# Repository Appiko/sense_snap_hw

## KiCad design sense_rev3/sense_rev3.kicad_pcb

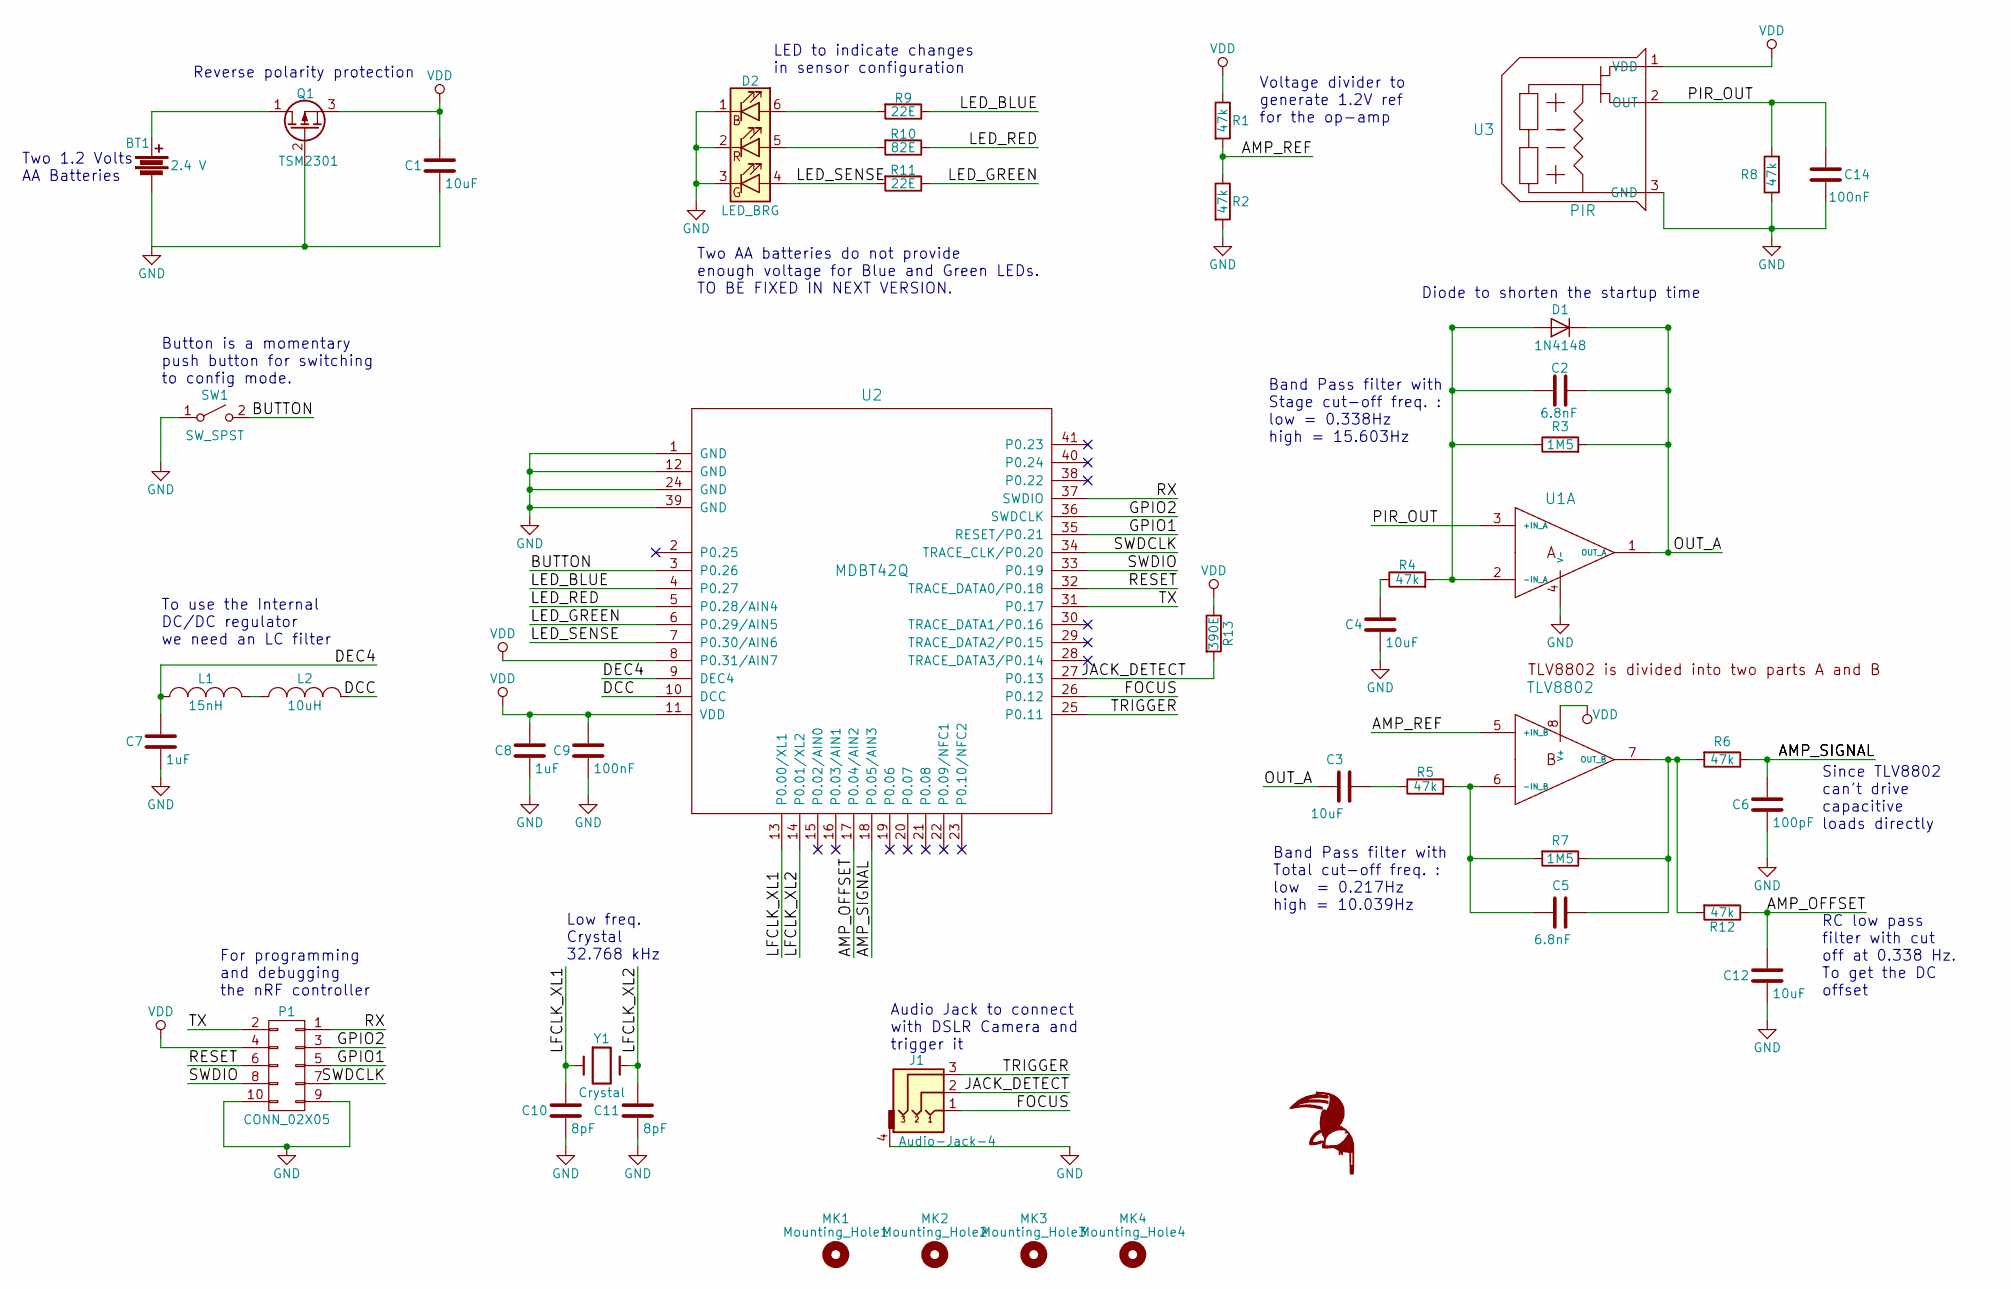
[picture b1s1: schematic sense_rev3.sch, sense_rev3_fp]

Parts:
BT1: 2.4 V; Molex_KK-6410-02_02x2.54mm_Straight
C1, C3, C4, C12: 10uF; C_0805
C2, C5: 6.8nF; C_0805
C6: 100pF; C_0805
C7, C8: 1uF; C_0805
C9, C14: 100nF; C_0805
C10, C11: 8pF; C_0805
D1: 1N4148; D_MiniMELF
D2: LED_BRG; LED_RGB_5050-6
J1: Audio-Jack-4; Molex_KK-6410-04_04x2.54mm_Straight
L1: 15nH; L_0805
L2: 10uH; L_0805
MK1: Mounting_Hole1; MountingHole_3.2mm_M3
MK2: Mounting_Hole2; MountingHole_3.2mm_M3
MK3: Mounting_Hole3; MountingHole_3.2mm_M3
MK4: Mounting_Hole4; MountingHole_3.2mm_M3
P1: CONN_02X05; prog_connect
Q1: TSM2301; SOT-23
R1, R2, R4, R5, R6, R8, R12: 47k; R_0805
R3, R7: 1M5; R_0805
R9, R11: 22E; R_0805
R10: 82E; R_0805
R13: 390E; R_0805
SW1: SW_SPST; Molex_KK-6410-02_02x2.54mm_Straight
U1: TLV8802; SSOP-8_2.95x2.8mm_Pitch0.65mm
U2: MDBT42Q; mdbt42Q
U3: PIR; PIR_TO5
Y1: Crystal; Crystal_C38-LF_d3.0mm_l8.0mm_Horizontal

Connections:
/AMP_OFFSET: C12.1, R12.1, U2.17 (P0.04/AIN2)
/AMP_REF: R1.2, R2.1, U1.5 (+IN_B)
/AMP_SIGNAL: C6.1, R6.1, U2.18 (P0.05/AIN3)
/BUTTON: SW1.2 (B), U2.3 (P0.26)
/DCC: L2.2, U2.10 (DCC)
/DEC4: C7.1, L1.1, U2.9 (DEC4)
/FOCUS: J1.1, U2.26 (P0.12)
/GPIO1: P1.5, U2.35 (RESET/P0.21)
/GPIO2: P1.3, U2.36 (SWDCLK)
/JACK_DETECT: J1.2, R13.2, U2.27 (P0.13)
/LED_BLUE: R9.1, U2.4 (P0.27)
/LED_GREEN: R11.1, U2.6 (P0.29/AIN5)
/LED_RED: R10.1, U2.5 (P0.28/AIN4)
/LED_SENSE: D2.4 (BA), R11.2, U2.7 (P0.30/AIN6)
/LFCLK_XL1: C10.1, U2.13 (P0.00/XL1), Y1.1
/LFCLK_XL2: C11.1, U2.14 (P0.01/XL2), Y1.2
/OUT_A: C2.2, C3.1, D1.1 (K), R3.2, U1.1 (OUT_A)
/PIR_OUT: C14.2, R8.2, U1.3 (+IN_A), U3.2 (OUT)
/RESET: P1.6, U2.32 (TRACE_DATA0/P0.18)
/RX: P1.1, U2.37 (SWDIO)
/SWDCLK: P1.7, U2.34 (TRACE_CLK/P0.20)
/SWDIO: P1.8, U2.33 (P0.19)
/TRIGGER: J1.3, U2.25 (P0.11)
/TX: P1.2, U2.31 (P0.17)
GND: BT1.2, C1.2, C4.2, C6.2, C7.2, C8.2, C9.2, C10.2, C11.2, C12.2, C14.1, D2.1 (RK), D2.2 (GK), D2.3 (BK), J1.4, P1.9, P1.10, Q1.2 (G), R2.2, R8.1, SW1.1 (A), U1.4 (V-), U2.1 (GND), U2.12 (GND), U2.24 (GND), U2.39 (GND), U3.3 (GND)
unnamed: BT1.1, Q1.1 (D)
unnamed: C2.1, D1.2 (A), R3.1, R4.2, U1.2 (-IN_A)
unnamed: C3.2, R5.1
unnamed: C4.1, R4.1
unnamed: C5.1, R6.2, R7.1, R12.2, U1.7 (OUT_B)
unnamed: C5.2, R5.2, R7.2, U1.6 (-IN_B)
unnamed: D2.5 (GA), R10.2
unnamed: D2.6 (RA), R9.2
unnamed: L1.2, L2.1
VDD: C1.1, C8.1, C9.1, P1.4, Q1.3 (S), R1.1, R13.1, U1.8 (V+), U2.8 (P0.31/AIN7), U2.11 (VDD), U3.1 (VDD)

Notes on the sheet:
Reverse polarity protection
Two 1.2 Volts AA Batteries
Button is a momentary push button for switching to config mode.
To use the Internal DC/DC regulator we need an LC filter
For programming and debugging the nRF controller
Low freq. Crystal 32.768 kHz
Audio Jack to connect with DSLR Camera and trigger it
Band Pass filter with Total cut-off freq. : low = 0.217Hz high = 10.039Hz
Band Pass filter with Stage cut-off freq. : low = 0.338Hz high = 15.603Hz
Since TLV8802 can't drive capacitive loads directly
RC low pass filter with cut off at 0.338 Hz. To get the DC offset
Diode to shorten the startup time
Voltage divider to generate 1.2V ref for the op-amp
LED to indicate changes in sensor configuration
Two AA batteries do not provide enough voltage for Blue and Green LEDs. TO BE FIXED IN NEXT VERSION.

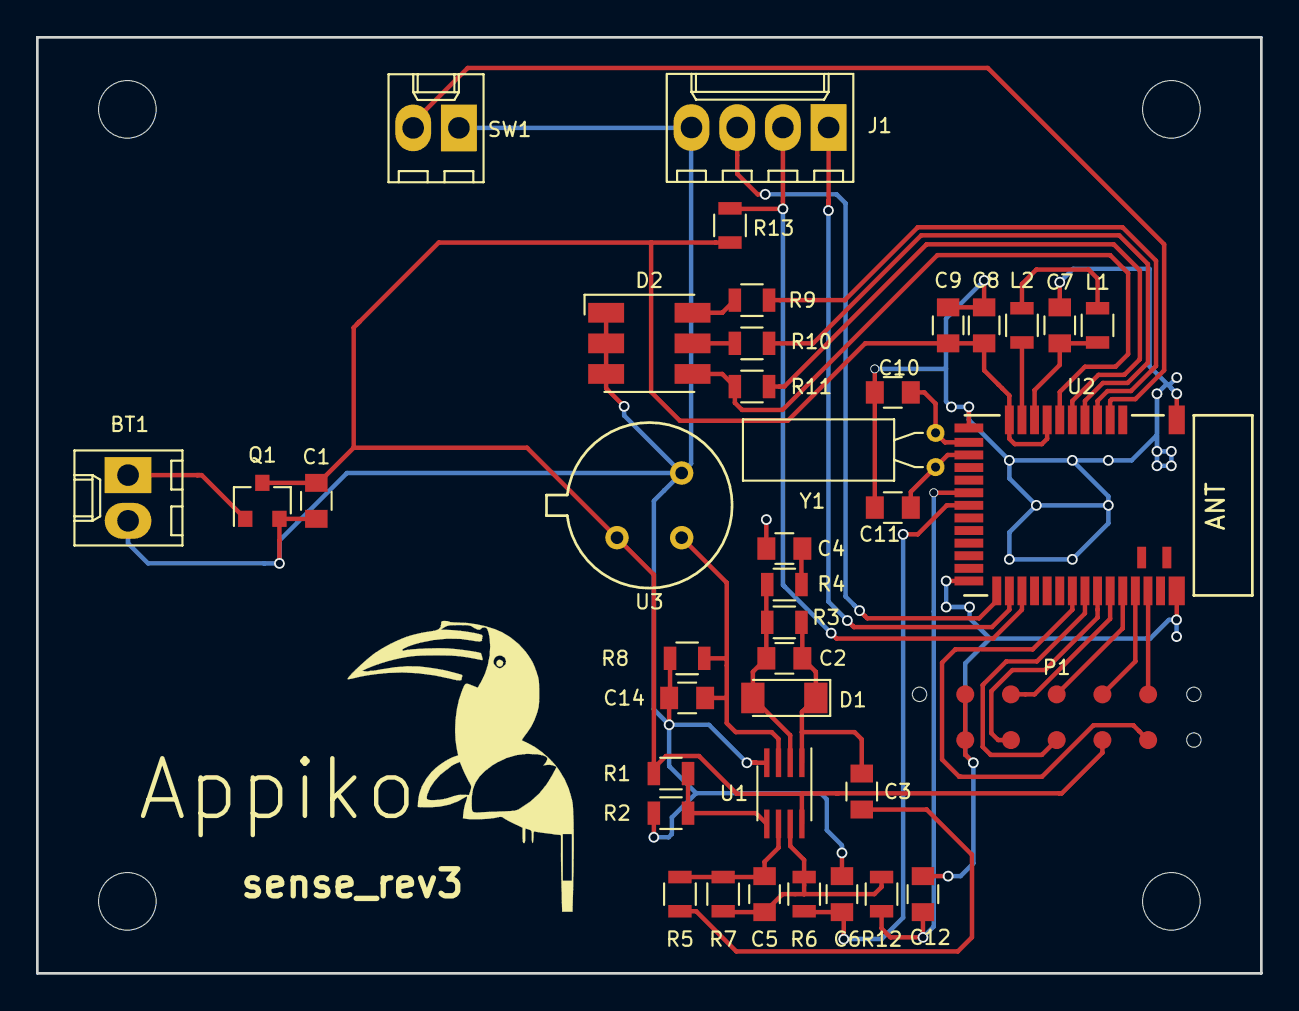
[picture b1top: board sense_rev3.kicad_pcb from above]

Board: 2 copper layers, 68.0 x 52.0 mm, 43 parts (0 on the bottom side), 35 nets.

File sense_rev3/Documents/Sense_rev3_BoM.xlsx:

Designator | Value | Package | Board
U3 | PIR | sense_rev3_fp:PIR_TO5 | sense_rev3 | PIR
Q1 | TSM2301/IRLML6401 | sense_rev3_fp:SOT-23 | sense_rev3 | Q_PMOS_DGS
BT1 | 2.4 V | sense_rev3_fp:Molex_KK-6410-02_02x2.54mm_Straight | sense_rev3 | Battery
P1 | CONN_02X05 | sense_rev3_fp:prog_connect | sense_rev3 | CONN_02X05
L2 | 10uH | sense_rev3_fp:L_0805 | sense_rev3 | INDUCTOR_SMALL
U2 | MDBT42Q | sense_rev3_fp:mdbt42Q | sense_rev3 | MDBT42Q
R1 | 47k | sense_rev3_fp:R_0805 | sense_rev3 | R
C11 | 8pF | sense_rev3_fp:C_0805 | sense_rev3 | C
C6 | 100pF | sense_rev3_fp:C_0805 | sense_rev3 | C
R7 | 1M5 | sense_rev3_fp:R_0805 | sense_rev3 | R
L1 | 15nH | sense_rev3_fp:L_0805 | sense_rev3 | INDUCTOR_SMALL
C10 | 8pF | sense_rev3_fp:C_0805 | sense_rev3 | C
C7 | 1uF | sense_rev3_fp:C_0805 | sense_rev3 | C
C9 | 100nF | sense_rev3_fp:C_0805 | sense_rev3 | C
C8 | 1uF | sense_rev3_fp:C_0805 | sense_rev3 | C
C3 | 10uF | sense_rev3_fp:C_0805 | sense_rev3 | C
C2 | 6.8nF | sense_rev3_fp:C_0805 | sense_rev3 | C
R5 | 47k | sense_rev3_fp:R_0805 | sense_rev3 | R
R3 | 1M5 | sense_rev3_fp:R_0805 | sense_rev3 | R
C4 | 10uF | sense_rev3_fp:C_0805 | sense_rev3 | C
R4 | 47k | sense_rev3_fp:R_0805 | sense_rev3 | R
D1 | 1N4148 | sense_rev3_fp:D_MiniMELF | sense_rev3 | D
C1 | 10uF | sense_rev3_fp:C_0805 | sense_rev3 | C
R8 | 47k | sense_rev3_fp:R_0805 | sense_rev3 | R
R2 | 47k | sense_rev3_fp:R_0805 | sense_rev3 | R
R6 | 47k | sense_rev3_fp:R_0805 | sense_rev3 | R
C5 | 6.8nF | sense_rev3_fp:C_0805 | sense_rev3 | C
D2 | LED_BRG | sense_rev3_fp:LED_RGB_5050-6 | sense_rev3 | LED_BRG
Y1 | Crystal | sense_rev3_fp:Crystal_C38-LF_d3.0mm_l8.0mm_Horizontal | sense_rev3 | Crystal
C14 | 100nF | sense_rev3_fp:C_0805 | sense_rev3 | C
R9 | 22E | sense_rev3_fp:R_0805 | sense_rev3 | R
R10 | 82E | sense_rev3_fp:R_0805 | sense_rev3 | R
R11 | 22E | sense_rev3_fp:R_0805 | sense_rev3 | R
SW1 | SW_SPST | sense_rev3_fp:Molex_KK-6410-02_02x2.54mm_Straight | sense_rev3 | SW_SPST
U1 | TLV8802 | sense_rev3_fp:SSOP-8_2.95x2.8mm_Pitch0.65mm | sense_rev3 | TLV8802
R12 | 47k | sense_rev3_fp:R_0805 | sense_rev3 | R
C12 | 10uF | sense_rev3_fp:C_0805 | sense_rev3 | C
J1 | Audio-Jack-4 | sense_rev3_fp:Molex_KK-6410-04_04x2.54mm_Straight | sense_rev3 | Audio-Jack-4
R13 | 390E | sense_rev3_fp:R_0805 | sense_rev3 | R
MK1 | Mounting_Hole1 | sense_rev3_fp:MountingHole_3.2mm_M3 | sense_rev3 | Mounting_Hole
MK2 | Mounting_Hole2 | sense_rev3_fp:MountingHole_3.2mm_M3 | sense_rev3 | Mounting_Hole
MK3 | Mounting_Hole3 | sense_rev3_fp:MountingHole_3.2mm_M3 | sense_rev3 | Mounting_Hole
MK4 | Mounting_Hole4 | sense_rev3_fp:MountingHole_3.2mm_M3 | sense_rev3 | Mounting_Hole

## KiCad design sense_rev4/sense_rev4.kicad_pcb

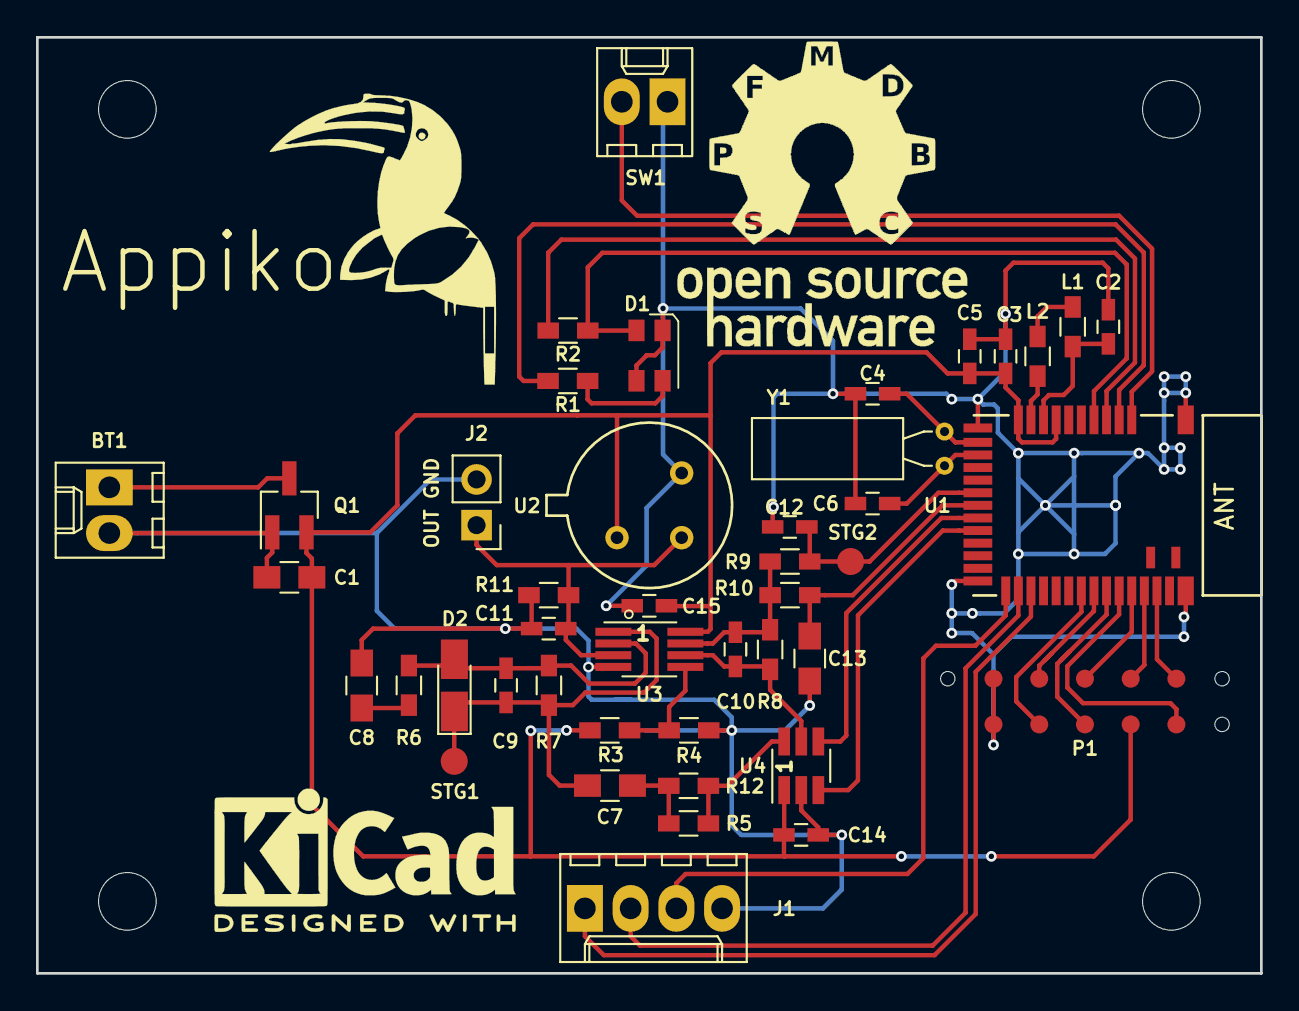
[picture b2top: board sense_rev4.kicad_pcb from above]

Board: 2 copper layers, 68.0 x 52.0 mm, 44 parts (0 on the bottom side), 36 nets.

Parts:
BT1: Battery; Molex_KK-6410-02_02x2.54mm_Straight
C1: 10uF; C_0805_HandSoldering
C2, C3: 1uF; C_0603_HandSoldering
C4, C6: 8pF; C_0603_HandSoldering
C5, C11: 100nF; C_0603_HandSoldering
C7, C8, C13: 22uF; C_0805_HandSoldering
C9, C10: 6.8nF; C_0603_HandSoldering
C12: 100pF; C_0603_HandSoldering
C14, C15: 0.1uF; C_0603_HandSoldering
D1: LED_GREEN/RED; XZMDKVG45S(V4-X)
D2: 1N4148; D_MicroMELF_Hadsoldering
J1: Audio-Jack-4; Molex_KK-6410-04_04x2.54mm_Straight
J2: Conn_01x02; Pin_Header_Straight_1x02_Pitch2.54mm
L1: 15nH; L_0603_HandSoldering
L2: 10nH; L_0603_HandSoldering
P1: CONN_02X05; prog_connect
Q1: Q_PMOS_DGS; SOT-23_Handsoldering
R1, R2: 22E; R_0603_HandSoldering
R3, R4, R7, R8: 1M5; R_0603_HandSoldering
R5, R6, R9, R10, R12: 33k; R_0603_HandSoldering
R11: 47k; R_0603_HandSoldering
STG1, STG2: TEST; Measurement_Point_Round-SMD-Pad_Small
SW1: SW_SPST; Molex_KK-6410-02_02x2.54mm_Straight
U1: MDBT42Q; mdbt42Q
U2: PIR; PIR_TO5
U3: TLV8802; SSOP-8_2.95x2.8mm_Pitch0.65mm_Hand_Soldering
U4: MCP4012T-503E/CH; SOT-23-6_Handsoldering
Y1: Crystal; Crystal_C38-LF_d3.0mm_l8.0mm_Horizontal

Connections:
/AMP_OFFSET: C13.2, R10.1, U1.18
/AMP_REF: R3.2, R4.1, U3.5
/AMP_SIGNAL: C12.2, R9.1, STG2.1, U1.17
/AUDIO_JACK_IO: J1.C, U1.25
/BUTTON: SW1.2, U1.2
/DCC: L2.2, U1.10
/DEC4: C2.2, L1.1, U1.9
/FOCUS: J1.B, U1.26
/GPIO1: P1.6, U1.33
/GPIO2: P1.7, U1.32
/LED_GREEN: R2.1, U1.4
/LED_RED: R1.2, U1.3
/LED_SENSE: D1.4, R2.2, U1.5
/LFCLK_XL1: C4.2, U1.13, Y1.1
/LFCLK_XL2: C6.2, U1.14, Y1.2
/MCP4012T_CS: U1.20, U4.3
/MCP4012T_U/d: U1.19, U4.4
/OUT_A: C7.2, C9.1, D2.1, R7.1, STG1.1, U3.1
/PIR_OUT: C11.1, J2.1, R11.1, U2.2, U3.3
/RESET: P1.5, U1.35
/RX: P1.8, U1.31
/SWDCLK: P1.3, U1.36
/SWDIO: P1.1, U1.37
/TRIGGER: J1.A, U1.27
/TX: P1.2, U1.34
GND: BT1.2, C1.2, C2.1, C3.1, C4.1, C5.1, C6.1, C8.2, C11.2, C12.1, C13.1, C14.2, C15.2, D1.1, D1.3, J1.D, J2.2, P1.9, P1.10, Q1.1, R4.2, R11.2, SW1.1, U1.1, U1.12, U1.24, U1.39, U2.3, U3.4, U4.2
unnamed: BT1.1, Q1.3
unnamed: C7.1, R5.2, R12.2
unnamed: C8.1, R6.2
unnamed: C9.2, D2.2, R6.1, R7.2, U3.2
unnamed: C10.1, R8.1, R9.2, R10.2, U3.7
unnamed: C10.2, R8.2, U3.6, U4.5
unnamed: D1.2, R1.1
unnamed: L1.2, L2.1
unnamed: R5.1, R12.1, U4.6
VDD: C1.1, C3.2, C5.2, C14.1, C15.1, P1.4, Q1.2, R3.1, U1.8, U1.11, U2.1, U3.8, U4.1

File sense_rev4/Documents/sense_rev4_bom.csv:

Component,Description,Part,References,Value,Footprint,Quantity Per PCB,Datasheet
1,,Battery-sense_rev3-sense_rev4-rescue-sense_rev4-rescue,BT1,Battery,Molex_KK-6410-02_02x2.54mm_Straight,1,
2,,C-sense_rev3-sense_rev4-rescue-sense_rev4-rescue,C5 C11 C14 C15,100nF,C_0603_HandSoldering,4,
3,,C-sense_rev3-sense_rev4-rescue-sense_rev4-rescue,C12,100pF,C_0603_HandSoldering,1,
4,,C-sense_rev3-sense_rev4-rescue-sense_rev4-rescue,C1,10uF,C_0805_HandSoldering,1,
5,,C-sense_rev3-sense_rev4-rescue-sense_rev4-rescue,C2 C3,1uF,C_0603_HandSoldering,2,
6,,C-sense_rev3-sense_rev4-rescue-sense_rev4-rescue,C7 C8 C13,22uF,C_0805_HandSoldering,3,
7,,C-sense_rev3-sense_rev4-rescue-sense_rev4-rescue,C9 C10,6.8nF,C_0603_HandSoldering,2,
8,,C-sense_rev3-sense_rev4-rescue-sense_rev4-rescue,C4 C6,8pF,C_0603_HandSoldering,2,
9,,LED_GREEN_RED-RESCUE-sense_rev4-sense_rev4-rescue-sense_rev4-rescue-sense_rev4-rescue,D1,XZMDKVG45S,XZMDKVG45S(V4-X),1,
10,,Audio-Jack-4-RESCUE-sense_rev4-sense_rev4-rescue-sense_rev4-rescue-sense_rev4-rescue,J1,Audio-Jack-4,Molex_KK-6410-04_04x2.54mm_Straight,1,
11,,INDUCTOR_SMALL-sense_rev3-sense_rev4-rescue-sense_rev4-rescue,L2,10nH,L_0603_HandSoldering,1,
12,,INDUCTOR_SMALL-sense_rev3-sense_rev4-rescue-sense_rev4-rescue,L1,15nH,L_0603_HandSoldering,1,
13,,CONN_02X05-sense_rev3-sense_rev4-rescue-sense_rev4-rescue,P1,CONN_02X05,prog_connect,1,
14,,Q_PMOS_DGS-RESCUE-sense_rev4-sense_rev4-rescue-sense_rev4-rescue-sense_rev4-rescue,Q1,TSM2301,SOT-23_Handsoldering,1,
15,,R-sense_rev3-sense_rev4-rescue-sense_rev4-rescue,R3 R4 R7 R8,1M5,R_0603_HandSoldering,4,
16,,R-sense_rev3-sense_rev4-rescue-sense_rev4-rescue,R1 R2,33E,R_0603_HandSoldering,2,
17,,R-sense_rev3-sense_rev4-rescue-sense_rev4-rescue,R5 R6 R9 R10 R12,33k,R_0603_HandSoldering,5,
18,,R-sense_rev3-sense_rev4-rescue-sense_rev4-rescue,R11,47k,R_0603_HandSoldering,1,
19,,SW_SPST-sense_rev3-sense_rev4-rescue-sense_rev4-rescue,SW1,SW_SPST,Molex_KK-6410-02_02x2.54mm_Straight,1,
20,,MCP4012T-503E_CH-RESCUE-sense_rev4-sense_rev4-rescue-sense_rev4-rescue-sense_rev4-rescue,U4,MCP4012T-503E/CH,SOT-23-6_Handsoldering,1,
21,,MDBT42Q-sense_rev3-sense_rev4-rescue-sense_rev4-rescue,U1,MDBT42Q,mdbt42Q,1,
22,,PIR-sense_rev3-sense_rev4-rescue-sense_rev4-rescue,U2,PIR,PIR_TO5,1,
23,,TLV8802-RESCUE-sense_rev4-sense_rev4-rescue-sense_rev4-rescue-sense_rev4-rescue,U3,TLV8802,SSOP-8_2.95x2.8mm_Pitch0.65mm,1,
24,,Crystal-sense_rev3-sense_rev4-rescue-sense_rev4-rescue,Y1,Crystal,Crystal_C38-LF_d3.0mm_l8.0mm_Horizontal,1,
,,,,,,,
,,,,,,,
,,,,,,,
,,,,,,,
,,,,,,,
Component Groups:,24,,,,,,
Component Count:,40,,,,,,
Fitted Components:,40,,,,,,
Number of PCBs:,1,,,,,,
Total components:,40,,,,,,
Schematic Version:,,,,,,,
Schematic Date:,,,,,,,
BoM Date:,04/10/18 19:14:46,,,,,,
Schematic Source:,D:\Shubham_M\Appiko\GitHub\sense_snap_hw\sense_rev4\sense_rev4.sch,,,,,,
KiCad Version:,Eeschema (5.0-dev-4140-g2e42d5c00),,,,,,

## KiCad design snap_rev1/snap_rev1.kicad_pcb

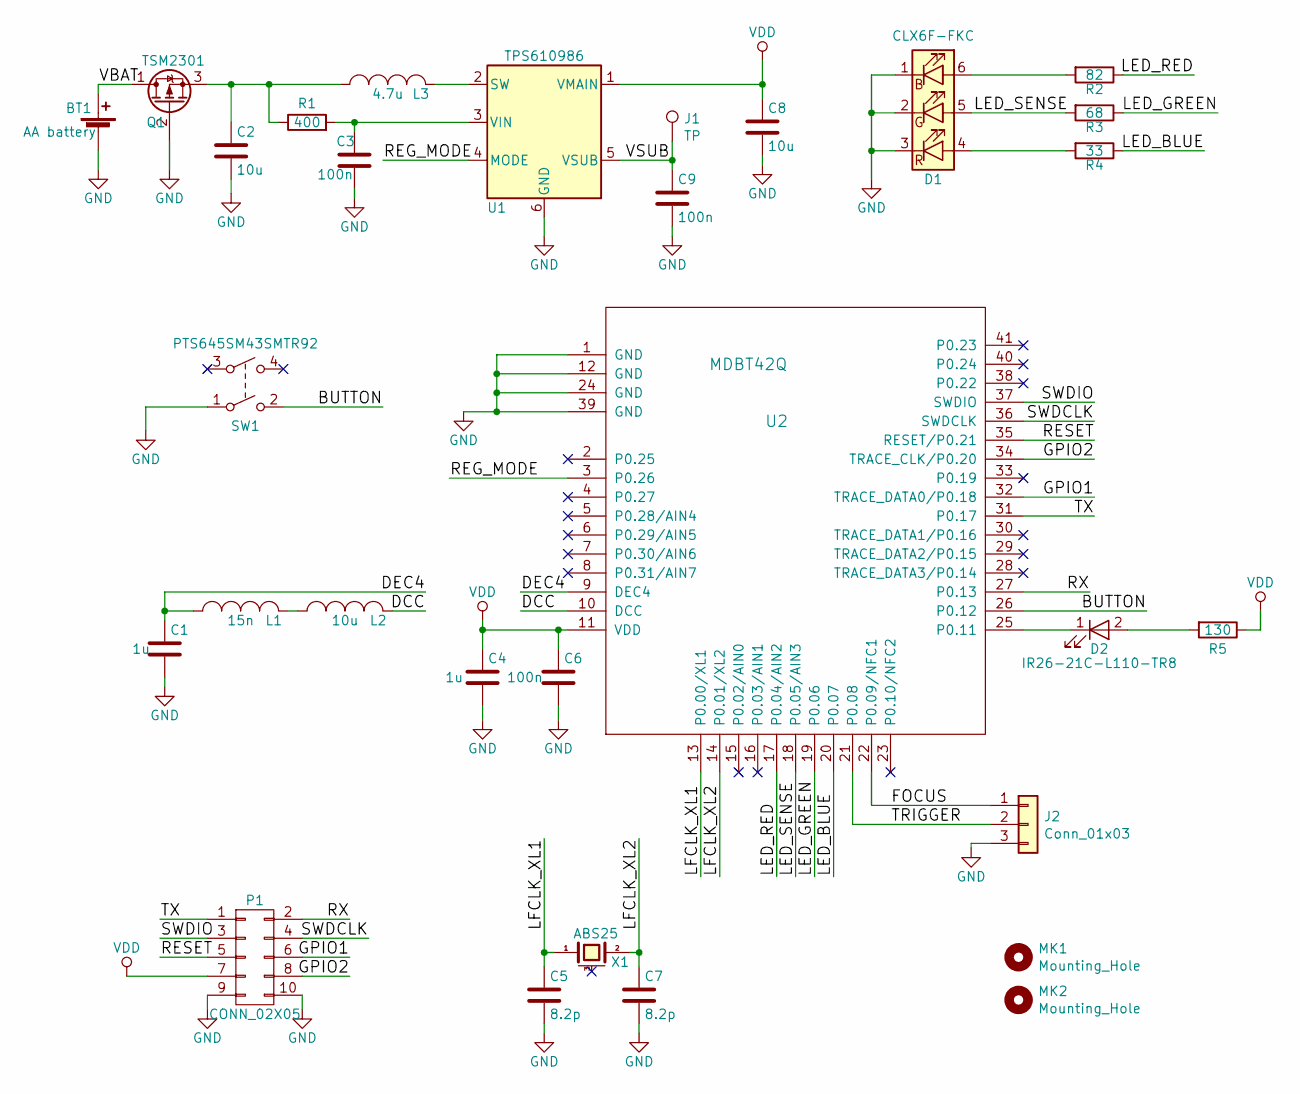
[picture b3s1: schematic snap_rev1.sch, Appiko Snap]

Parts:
BT1: AA battery; Pin_Header_Straight_1x02_Pitch2.54mm
C1, C4: 1u; C_0805
C2, C8: 10u; C_0805; Rating >10V
C3, C9: 100n; C_0805; Rating >10V
C5, C7: 8.2p; C_0603
C6: 100n; C_0805
D1: CLX6F-FKC; LED_RGB_PLCC-6; Part Number CLX6F-FKC
D2: IR26-21C-L110-TR8; IR26-21C-L110
J1: TP; Measurement_Point_Round-SMD-Pad_Small
J2: Conn_01x03; Molex_PicoBlade_53047-0310_03x1.25mm_Straight
L1: 15n; C_0603
L2: 10u; C_0805
L3: 4.7u; C_0805
MK1, MK2: Mounting_Hole; MountingHole_2.2mm_M2
P1: CONN_02X05; Socket_Strip_Straight_2x05_Pitch2.54mm_SMD
Q1: TSM2301; Part Number TSM2301CX
R1: 400; R_0805
R2: 82; R_0805
R3: 68; R_0805
R4: 33; R_0805
R5: 130; R_0805
SW1: PTS645SM43SMTR92; SMD_tactile_button; Part Number PTS645SM43SMTR92
U1: TPS610986; WSON6_1.5x1.5mm_Pitch0.5mm; Part Number TPS610986
U2: MDBT42Q; mdbt42Q
X1: ABS25; ABS25-32.768; Part Number ABS25-32.768KHZ-6-T

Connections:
/BUTTON: SW1.2, U2.26 (P0.12)
/DCC: L2.2, U2.10 (DCC)
/DEC4: C1.1, L1.1, U2.9 (DEC4)
/FOCUS: J2.1, U2.22 (P0.09/NFC1)
/GPIO1: P1.6, U2.32 (TRACE_DATA0/P0.18)
/GPIO2: P1.8, U2.34 (TRACE_CLK/P0.20)
/LED_BLUE: R4.1, U2.20 (P0.07)
/LED_GREEN: R3.1, U2.19 (P0.06)
/LED_RED: R2.1, U2.17 (P0.04/AIN2)
/LED_SENSE: D1.5 (GA), R3.2, U2.18 (P0.05/AIN3)
/LFCLK_XL1: C5.1, U2.13 (P0.00/XL1), X1.1
/LFCLK_XL2: C7.1, U2.14 (P0.01/XL2), X1.2
/REG_MODE: U1.4 (MODE), U2.3 (P0.26)
/RESET: P1.5, U2.35 (RESET/P0.21)
/RX: P1.2, U2.27 (P0.13)
/SWDCLK: P1.4, U2.36 (SWDCLK)
/SWDIO: P1.3, U2.37 (SWDIO)
/TRIGGER: J2.2, U2.21 (P0.08)
/TX: P1.1, U2.31 (P0.17)
/VBAT: BT1.1 (+), Q1.1 (D)
/VSUB: C9.1, J1.1, U1.5 (VSUB)
GND: BT1.2 (-), C1.2, C2.2, C3.2, C4.2, C5.2, C6.2, C7.2, C8.2, C9.2, D1.1 (RK), D1.2 (GK), D1.3 (BK), J2.3, P1.9, P1.10, Q1.2 (G), SW1.1, U1.6 (GND), U2.1 (GND), U2.12 (GND), U2.24 (GND), U2.39 (GND)
unnamed: C2.1, L3.1, Q1.3 (S), R1.1
unnamed: C3.1, R1.2, U1.3 (VIN)
unnamed: D1.4 (BA), R4.2
unnamed: D1.6 (RA), R2.2
unnamed: D2.1 (K), U2.25 (P0.11)
unnamed: D2.2 (A), R5.2
unnamed: L1.2, L2.1
unnamed: L3.2, U1.2 (SW)
VDD: C4.1, C6.1, C8.1, P1.7, R5.1, U1.1 (VMAIN), U2.11 (VDD)

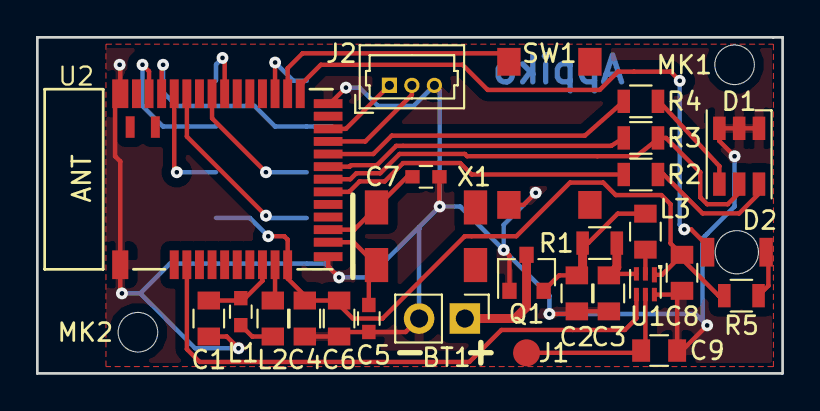
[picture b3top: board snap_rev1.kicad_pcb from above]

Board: 2 copper layers, 41.4 x 18.7 mm, 30 parts (1 on the bottom side), 31 nets.

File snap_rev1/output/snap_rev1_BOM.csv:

Reference,Quantity,Value,Rating,Part Number,Datasheet
U2,1,MDBT42Q,,,http://www.raytac.com/download/MDBT42/MDBT42Q-Version%20B.pdf
C2,C8,2,10u,>10V,
C6,1,100n,,,
C1,C4,2,1u,,
L2,1,10u,,,
L1,1,15n,,,
C5,C7,2,8.2p,,
P1,1,CONN_02X05,,,
Q1,1,TSM2301,,TSM2301CX,http://www.farnell.com/datasheets/2044652.pdf
X1,1,ABS25,,ABS25-32.768KHZ-6-T,http://www.abracon.com/Resonators/abs25.pdf
D2,1,IR26-21C-L110-TR8,,,http://www.everlight.com/file/ProductFile/IR26-21C-L110-TR8.pdf
R2,1,82,,,
R3,1,68,,,
R4,1,33,,,
R5,1,130,,,
BT1,1,AA battery,,,
J1,1,TP,,,
L3,1,4.7u,,,
R1,1,400,,,
C3,C9,2,100n,>10V,
J2,1,Conn_01x03,,,
U1,1,TPS610986,,TPS610986,http://www.ti.com/lit/ds/symlink/tps610985.pdf
SW1,1,PTS645SM43SMTR92,,PTS645SM43SMTR92,
D1,1,CLX6F-FKC,,CLX6F-FKC,http://www.cree.com/led-components/media/documents/ds-CLX6F-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
MK1,MK2,2,Mounting_Hole,,

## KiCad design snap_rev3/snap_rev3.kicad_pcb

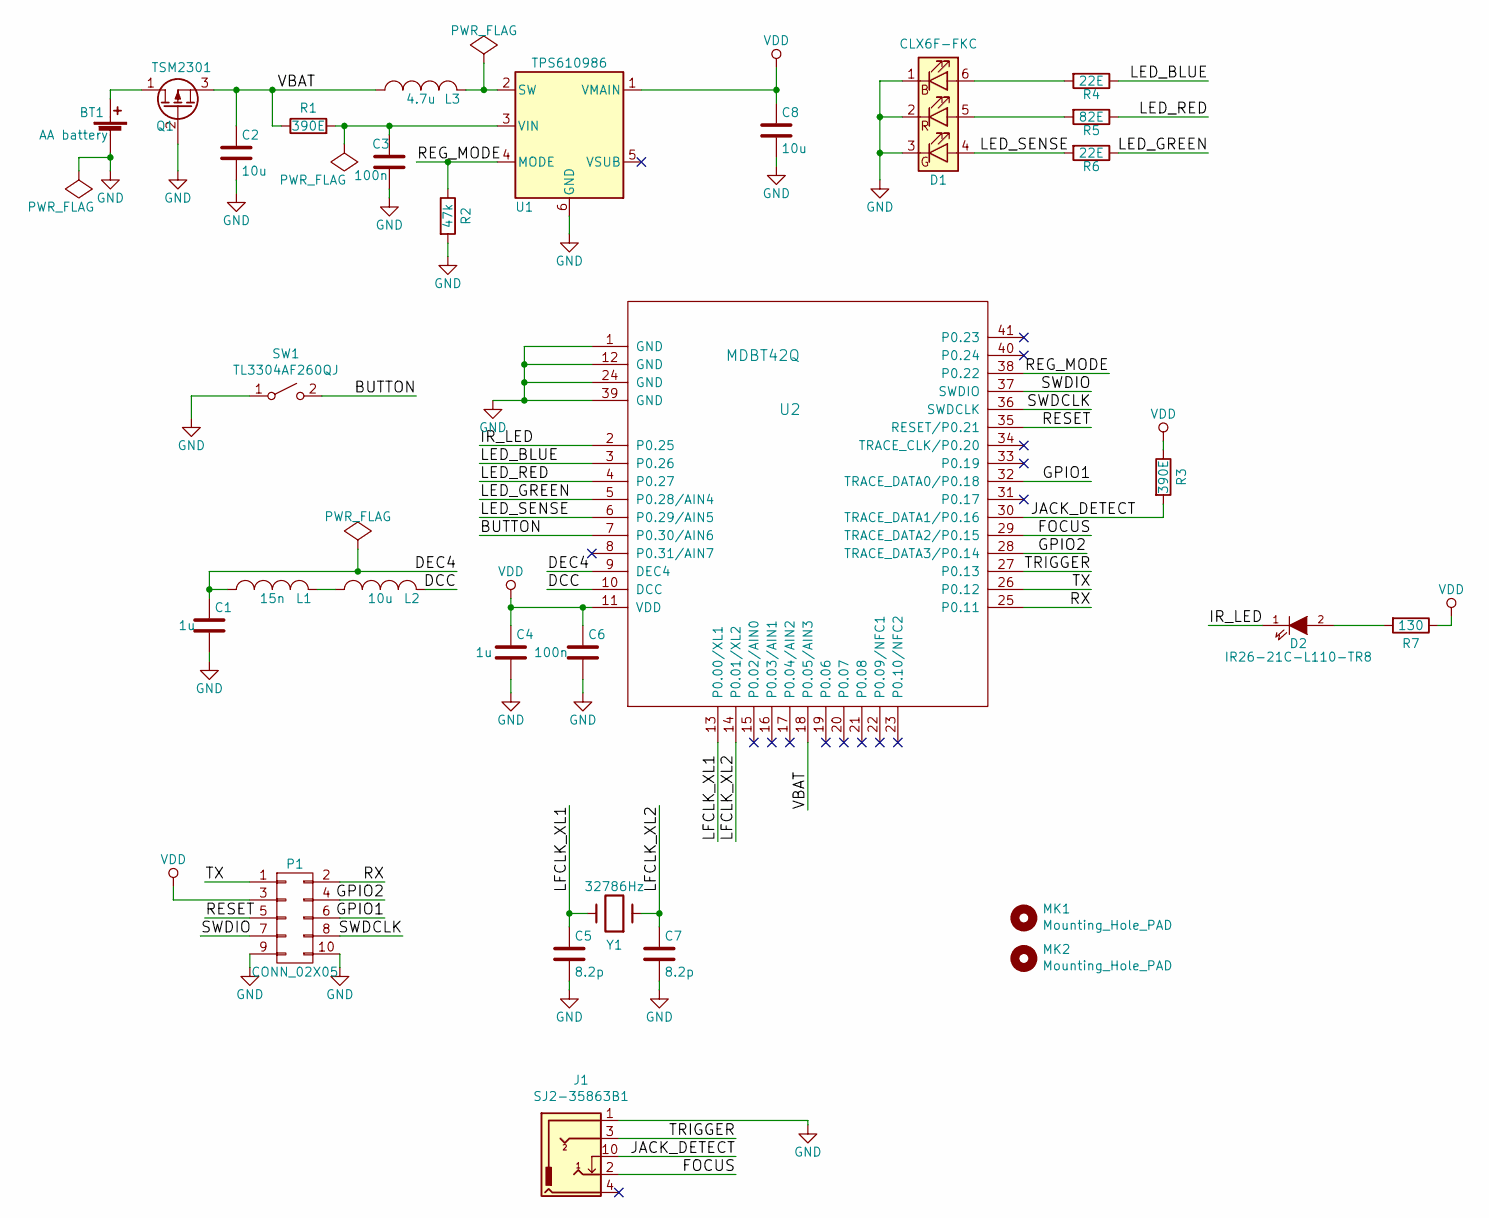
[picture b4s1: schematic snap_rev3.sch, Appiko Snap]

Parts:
BT1: AA battery; AA_keystone_206
C1, C4: 1u; C_0805
C2, C8: 10u; C_0805; Rating >10V
C3: 100n; C_0805; Rating >10V
C5, C7: 8.2p; C_0805
C6: 100n; C_0805
D1: CLX6F-FKC; LED_RGB_5050-6; Part Number CLX6F-FKC
D2: IR26-21C-L110-TR8; IR26-21C-L110_5mm-TH
J1: SJ2-35863B1; SJ2-35863B1-SMT
L1: 15n; C_0603
L2: 10u; C_0805
L3: 4.7u; C_0805
MK1, MK2: Mounting_Hole_PAD; MountingHole_1.7mm_M1.6
P1: CONN_02X05; prog_connect
Q1: TSM2301; Part Number TSM2301CX
R1, R3: 390E; R_0805
R2: 47k; R_0805
R4, R6: 22E; R_0805
R5: 82E; R_0805
R7: 130; R_0805
SW1: TL3304AF260QJ; SW_SPST_B3SL-1002P
U1: TPS610986; WSON6_1.5x1.5mm_Pitch0.5mm; Part Number TPS610986
U2: MDBT42Q; mdbt42Q
Y1: 32786Hz; Crystal_C38-LF_d3.0mm_l8.0mm_Horizontal

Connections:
/BUTTON: SW1.2 (B), U2.7 (P0.30/AIN6)
/DCC: L2.2, U2.10 (DCC)
/DEC4: C1.1, L1.1, U2.9 (DEC4)
/FOCUS: J1.2, U2.29 (TRACE_DATA2/P0.15)
/GPIO1: P1.6, U2.32 (TRACE_DATA0/P0.18)
/GPIO2: P1.4, U2.28 (TRACE_DATA3/P0.14)
/IR_LED: D2.1 (K), U2.2 (P0.25)
/JACK_DETECT: J1.10, R3.2, U2.30 (TRACE_DATA1/P0.16)
/LED_BLUE: R4.1, U2.3 (P0.26)
/LED_GREEN: R6.1, U2.5 (P0.28/AIN4)
/LED_RED: R5.1, U2.4 (P0.27)
/LED_SENSE: D1.4 (BA), R6.2, U2.6 (P0.29/AIN5)
/LFCLK_XL1: C5.1, U2.13 (P0.00/XL1), Y1.2
/LFCLK_XL2: C7.1, U2.14 (P0.01/XL2), Y1.1
/REG_MODE: R2.1, U1.4 (MODE), U2.38 (P0.22)
/RESET: P1.5, U2.35 (RESET/P0.21)
/RX: P1.2, U2.25 (P0.11)
/SWDCLK: P1.8, U2.36 (SWDCLK)
/SWDIO: P1.7, U2.37 (SWDIO)
/TRIGGER: J1.3, U2.27 (P0.13)
/TX: P1.1, U2.26 (P0.12)
/VBAT: C2.1, L3.1, Q1.3 (S), R1.1, U2.18 (P0.05/AIN3)
GND: BT1.2 (-), C1.2, C2.2, C3.2, C4.2, C5.2, C6.2, C7.2, C8.2, D1.1 (RK), D1.2 (GK), D1.3 (BK), J1.1, P1.9, P1.10, Q1.2 (G), R2.2, SW1.1 (A), U1.6 (GND), U2.1 (GND), U2.12 (GND), U2.24 (GND), U2.39 (GND)
unnamed: BT1.1 (+), Q1.1 (D)
unnamed: C3.1, R1.2, U1.3 (VIN)
unnamed: D1.5 (GA), R5.2
unnamed: D1.6 (RA), R4.2
unnamed: D2.2 (A), R7.2
unnamed: L1.2, L2.1
unnamed: L3.2, U1.2 (SW)
VDD: C4.1, C6.1, C8.1, P1.3, R3.1, R7.1, U1.1 (VMAIN), U2.11 (VDD)

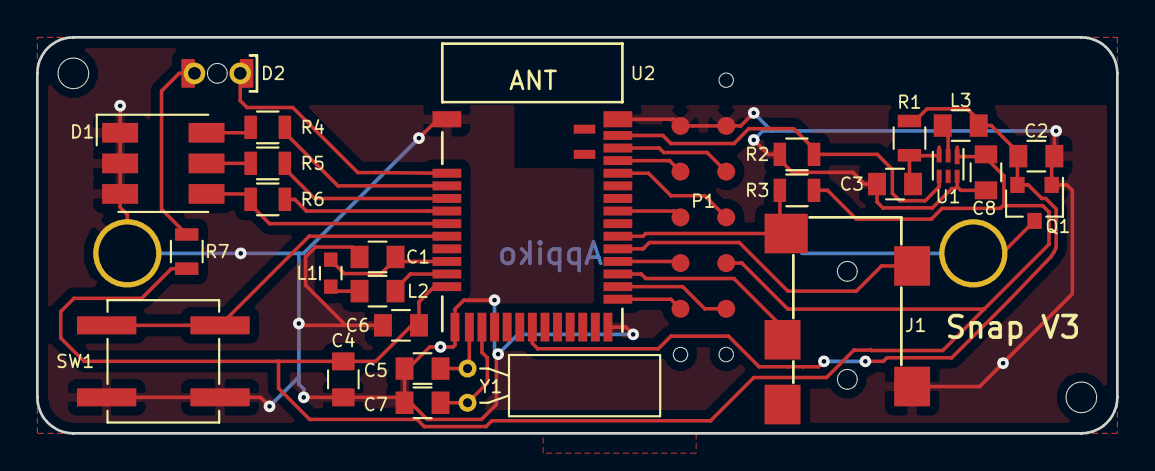
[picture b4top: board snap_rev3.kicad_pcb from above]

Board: 2 copper layers, 60.0 x 22.0 mm, 30 parts (1 on the bottom side), 31 nets.

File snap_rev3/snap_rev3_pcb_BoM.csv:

"Id";"Designator";"Package";"Quantity";"Designation";"Supplier and ref";
1;"Y1";"Crystal_C38-LF_d3.0mm_l8.0mm_Horizontal";1;"32786Hz";;;
2;"C5,C7";"C_0805";2;"8.2p";;;
3;"D2";"IR26-21C-L110_5mm-TH";1;"IR26-21C-L110-TR8";;;
4;"MK2,MK1";"MountingHole_1.7mm_M1.6";2;"Mounting_Hole_PAD";;;
5;"BT1";"AA_keystone_206";1;"AA battery";;;
6;"SW1";"SW_SPST_B3SL-1002P";1;"TL3304AF260QJ";;;
7;"D1";"LED_RGB_5050-6";1;"CLX6F-FKC";;;
8;"R5";"R_0805";1;"82E";;;
9;"P1";"prog_connect";1;"CONN_02X05";;;
10;"U2";"mdbt42Q";1;"MDBT42Q";;;
11;"U1";"WSON6_1.5x1.5mm_Pitch0.5mm";1;"TPS610986";;;
12;"R7";"R_0805";1;"130";;;
13;"R6,R4";"R_0805";2;"22E";;;
14;"R3,R1";"R_0805";2;"390E";;;
15;"R2";"R_0805";1;"47k";;;
16;"Q1";"TSM2301";1;"TSM2301";;;
17;"L3";"C_0805";1;"4.7u";;;
18;"L2,C8,C2";"C_0805";3;"10u";;;
19;"L1";"C_0603";1;"15n";;;
20;"C6,C3";"C_0805";2;"100n";;;
21;"C4,C1";"C_0805";2;"1u";;;
22;"J1";"SJ2-35863B1-SMT";1;"SJ2-35863B1";;;
